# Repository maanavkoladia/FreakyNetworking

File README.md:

# FreakyNetworking

**FreakyNetworking** is a lightweight, embedded networking stack designed to run on **FreakyRTOS**. It provides essential networking protocols and integrates with FreakyRTOS. This is also an example of how to integrate FreakyRTOS into a project using GNU-ARM. 

## Features
- MAC layer implementation
- IPv4 stack
- UDP transport
- DHCP client for dynamic IP configuration
- ARP request/reply handling
- ICMP ping utility
- TCP support (in development)
- RTOS integration for task scheduling and synchronization

## Supported Hardware
- TI `TM4C` microcontroller series
- Microchip WILC1000 WiFi module (SPI interface)
- There is a SPI breakout KiCad layout for the WILC1000 in the hw/ folder.

## Architecture & RTOS Integration
FreakyNetworking is tightly integrated with **FreakyRTOS**. It uses RTOS primitives such as tasks, semaphores, and timers to manage networking operations efficiently. 

The FreakyRTOS and FreakyNetworking are also integrated with **TivaWare** and **ValvanoWare**, enabling low-level hardware abstraction and peripheral management on TM4C devices.

## Toolchain
FreakyNetworking is built using the **GNU ARM Toolchain**, making it suitable for open-source and cross-platform development environments.

## Roadmap
- Complete TCP implementation with connection management
- TLS/SSL support
- IPv6 protocol support
- Advanced power management integration

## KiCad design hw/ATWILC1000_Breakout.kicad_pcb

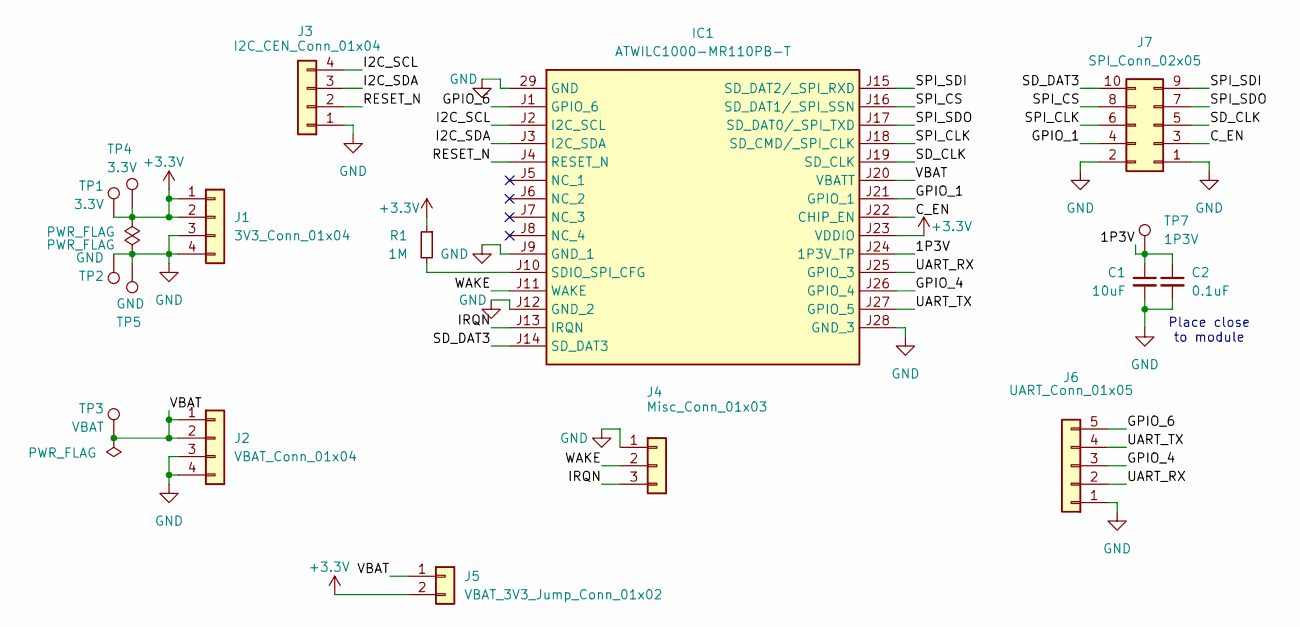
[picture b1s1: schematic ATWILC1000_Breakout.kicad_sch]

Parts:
C1: 10uF; C_0805_2012Metric_Pad1.18x1.45mm_HandSolder
C2: 0.1uF; C_0805_2012Metric_Pad1.18x1.45mm_HandSolder
IC1: ATWILC1000-MR110PB-T; ATWILC1000MR110PBT; Manufacturer_Part_Number ATWILC1000-MR110PB-T; Mouser Part Number 579-WILC1000MR110PBT
J1: 3V3_Conn_01x04; PinHeader_1x04_P2.54mm_Vertical
J2: VBAT_Conn_01x04; PinHeader_1x04_P2.54mm_Vertical
J3: I2C_CEN_Conn_01x04; PinHeader_1x04_P2.54mm_Vertical
J4: Misc_Conn_01x03; PinHeader_1x03_P2.54mm_Vertical
J5: VBAT_3V3_Jump_Conn_01x02; PinHeader_1x02_P2.54mm_Vertical
J6: UART_Conn_01x05; PinHeader_1x05_P2.54mm_Vertical
J7: SPI_Conn_02x05; PinHeader_2x05_P2.54mm_Vertical
R1: 1M; R_0805_2012Metric_Pad1.20x1.40mm_HandSolder
TP1, TP4: 3.3V; TestPoint_THTPad_1.5x1.5mm_Drill0.7mm
TP2, TP5: GND; TestPoint_THTPad_1.5x1.5mm_Drill0.7mm
TP3: VBAT; TestPoint_THTPad_1.5x1.5mm_Drill0.7mm
TP7: 1P3V; TestPoint_THTPad_1.5x1.5mm_Drill0.7mm

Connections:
+3.3V: IC1.J23 (VDDIO), J1.1, J1.2, J5.2, R1.1, TP1.1, TP4.1
/1P3V: C1.1, C2.1, IC1.J24 (1P3V_TP), TP7.1
/C_EN: IC1.J22 (CHIP_EN), J7.3
/GPIO_1: IC1.J21 (GPIO_1), J7.4
/GPIO_4: IC1.J26 (GPIO_4), J6.3
/GPIO_6: IC1.J1 (GPIO_6), J6.5
/I2C_SCL: IC1.J2 (I2C_SCL), J3.4
/I2C_SDA: IC1.J3 (I2C_SDA), J3.3
/IRQN: IC1.J13 (IRQN), J4.3
/RESET_N: IC1.J4 (RESET_N), J3.2
/SD_CLK: IC1.J19 (SD_CLK), J7.5
/SD_DAT3: IC1.J14 (SD_DAT3), J7.10
/SPI_CLK: IC1.J18 (SD_CMD/_SPI_CLK), J7.6
/SPI_CS: IC1.J16 (SD_DAT1/_SPI_SSN), J7.8
/SPI_SDI: IC1.J15 (SD_DAT2/_SPI_RXD), J7.9
/SPI_SDO: IC1.J17 (SD_DAT0/_SPI_TXD), J7.7
/UART_RX: IC1.J25 (GPIO_3), J6.2
/UART_TX: IC1.J27 (GPIO_5), J6.4
/VBAT: IC1.J20 (VBATT), J2.1, J2.2, J5.1, TP3.1
/WAKE: IC1.J11 (WAKE), J4.2
GND: C1.2, C2.2, IC1.29 (GND), IC1.J9 (GND_1), IC1.J12 (GND_2), IC1.J28 (GND_3), J1.3, J1.4, J2.3, J2.4, J3.1, J4.1, J6.1, J7.1, J7.2, TP2.1, TP5.1
unnamed: IC1.J10 (SDIO_SPI_CFG), R1.2

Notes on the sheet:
Place close to module

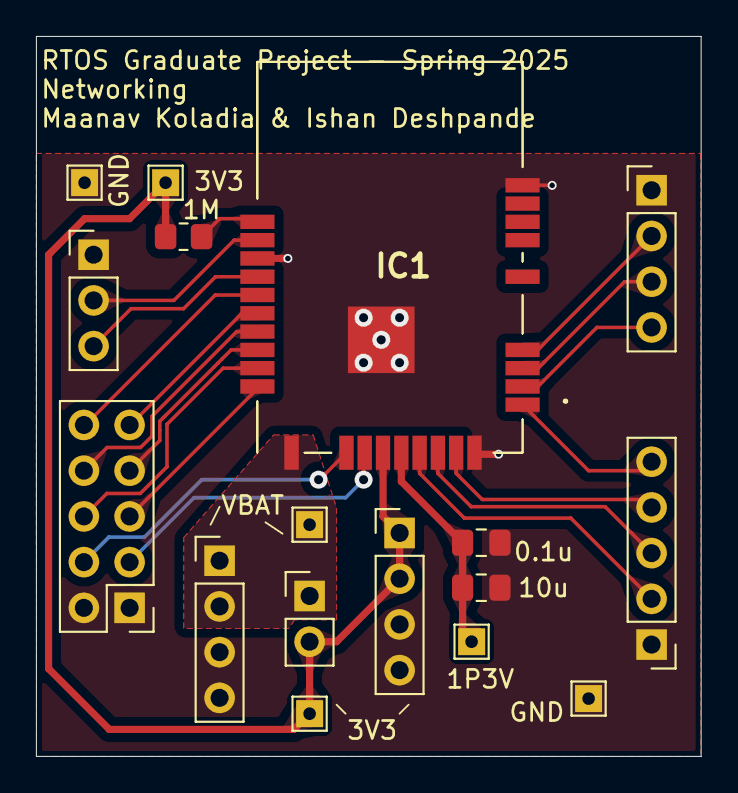
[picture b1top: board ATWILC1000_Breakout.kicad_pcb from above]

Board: 2 copper layers, 36.9 x 40.0 mm, 17 parts (0 on the bottom side), 22 nets.

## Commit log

2025-05-06 Chicken or th Egg?
2025-05-06 Updated the README
